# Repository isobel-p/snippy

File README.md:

# Snippy

Snippy is a USB dongle for taking screenshots, in a compact form factor. Often in class I have to take a bunch of screenshots of the teacher's presentations so I can make notes on them later. But doing that 10 times a day is boring. Why not make it fun with clicky tactile buttons? (Everything is better with clicky buttons.) The PCB is only 12x50mm!

## Features 
- Small size
- OS agnostic
- Fun to press

## BOM
|Part|QTY|Cost|
|---|---|---|
|PCB board|5|$21.56|
|Components|2|$10.79|
|PCBA|2|$15.89|
|Shipping||$5.37|
|Coupon||-$10.00|
|**Total**||$43.61|

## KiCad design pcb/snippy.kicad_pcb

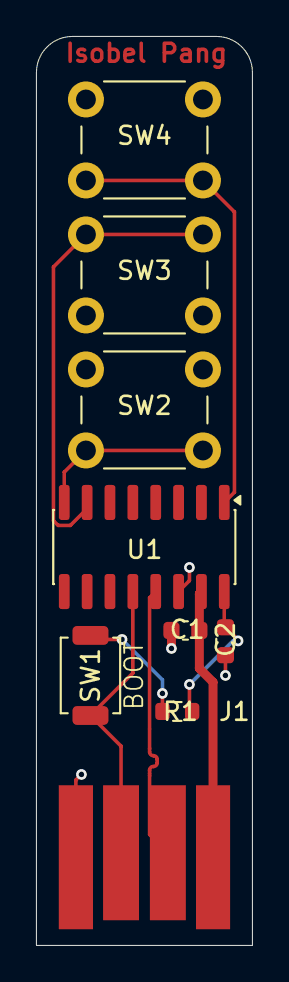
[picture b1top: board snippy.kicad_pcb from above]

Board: 2 copper layers, 12.0 x 50.5 mm, 9 parts (0 on the bottom side), 9 nets.

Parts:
C1, C2: 100nF; C_0603_1608Metric
J1: USB_A; USB-A
R1: 10k; R_0603_1608Metric
SW1: SW_Push; SW_SPST_TS-1088-xR020
SW2, SW3, SW4: SW_Push; SW_PUSH_6mm
U1: CH552G; SOIC-16_3.9x9.9mm_P1.27mm

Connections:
+3V3: C2.2, R1.1, U1.16 (3V3)
D+: J1.3 (D+), SW1.1, U1.12 (P3.6)
D-: J1.2 (D-), U1.13 (P3.7)
GND: C1.2, C2.1, J1.4 (GND), SW2.1, SW3.1, SW4.1, U1.14 (GND)
unnamed: R1.2, SW1.2
unnamed: SW2.2, U1.8 (P3.0)
unnamed: SW3.2, U1.7 (P3.1)
unnamed: SW4.2, U1.1 (P3.2)
VBUS: C1.1, J1.1 (VBUS), U1.15 (VCC)
